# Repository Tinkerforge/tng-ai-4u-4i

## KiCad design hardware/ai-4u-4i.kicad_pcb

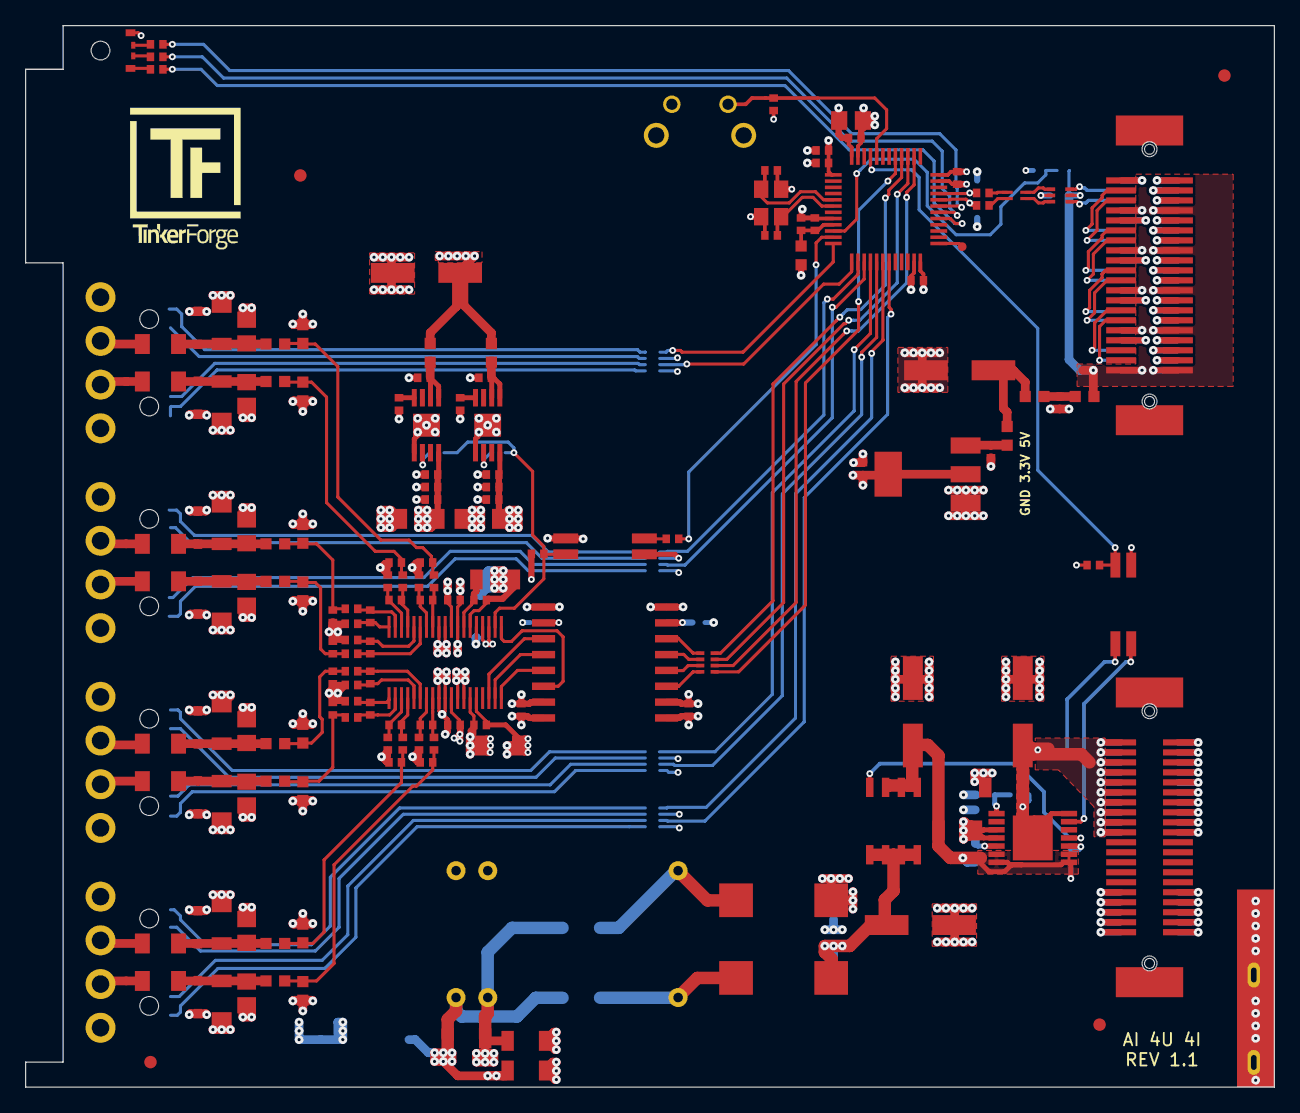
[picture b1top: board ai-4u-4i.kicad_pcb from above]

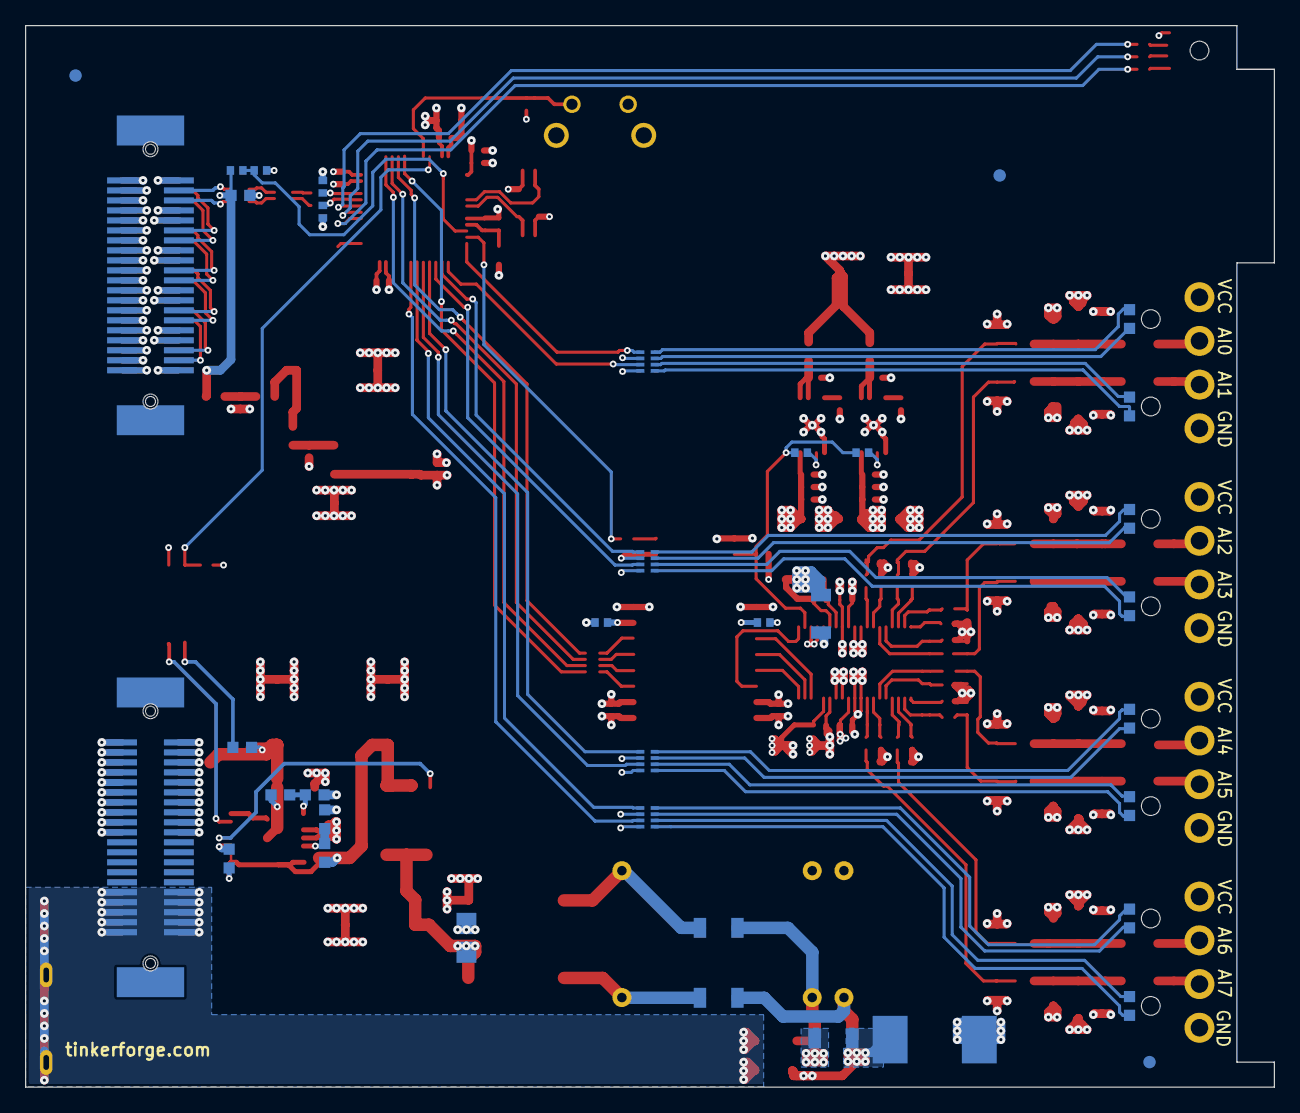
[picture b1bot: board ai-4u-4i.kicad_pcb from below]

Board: 4 copper layers, 100.0 x 85.0 mm, 206 parts (38 on the bottom side), 141 nets.

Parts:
C101, C102, C116, C117, C226, C227, C228, C229, C236, C237, C240, C241, C242, C243: 1uF; C0402F
C103, C104, C105, C106, C107, C112, C233, C235, C244, C245: 100nF; C0402F
C108, C109: 33pF; C0402F
C110: 10uF; C0805E
C111: 100uF; ELKO_63
C113, C114: 47pF; C0402F
C115: 2.2uF; C0603F
C118: 10uF/50V; C1206
C119, C120: 0; C1206
C121, C125, C126: 10uF/35V; C1206
C122, C123, C124, C234: 100uF/35V; ELKO_63
C127, C128: 1nF/2kV; C1206
C201, C202, C203, C204, C205, C206, C207, C208: 22nF; C1206
C209, C210, C211, C212, C213, C214, C215, C216: 2200pF; C0603F
C217, C218, C219, C220, C221, C222, C223, C224, C238, C239: 10nF; C0402F
C225, C232, C246: 22uF; C1206
C230, C231: 10uF; C1206
D101: 3.0SMI30CATR; SMC
D201, D202, D211, D212, D213, D214, D215, D216: CDSOD323-T12C; SOD-323
D203, D204, D205, D206, D207, D208, D209, D210: LED; LED-LP
Fiducial_Mark: VAL**; Fiducial_Mark
Fiducial_Mark#2, Fiducial_Mark#3, Fiducial_Mark#4, Fiducial_Mark#5, Fiducial_Mark#6, Fiducial_Mark#7: VAL**; Fiducial_Mark
J101: TNG-Power-TOP; TNG-40-TOP
J102: TNG-Power-BTM; TNG-40-BTM
J103: TNG-Data-TOP; TNG-40-TOP
J104: TNG-Data-BTM; TNG-40-BTM
L101: FB; R0603F
L102, L103, L104: INDUCTs; R0603F
L105: 744230900; WE-CNSW-0603
L201, L202: FB; C0603F
LED101: EASV3015RGBA0; LED-RGB-LP
P102: Debug; DEBUG_PAD
P103: PE; PE_Hook
P201: INPUT0; OQ_4P
P202: INPUT1; OQ_4P
P203: INPUT2; OQ_4P
P204: INPUT3; OQ_4P
Q101: FDS8449; SOIC-8-MOSFET
R101, R107, R108, R253: 1k; R0402F
R102, R105, R233, R235, R237, R239, R241, R243, R245, R247: 0; R0402F
R103, R104: 22; R0402F
R106: 56; R0402F
R109: 10k; R0402F
R110, R115: 10k; R0603F
R111, R112: DNP; R0603F
R113: 22; R0603F
R114: 68k; R0603F
R116: VC1206K201R030; R1206
R201, R202, R203, R204, R205, R206, R207, R208: 100; RMELF
R209, R211, R213, R215: DNP; R0805E
R210, R212, R214, R216: 124; R0805E
R217, R218, R219, R220, R221, R222, R223, R224: 1k; R0603F
R225, R226, R227, R228, R229, R230, R231, R232: 10M; R0402F
R234, R236, R238, R240, R242, R244, R246, R248: 1.1k; R0402F
R251, R252, R254: 4.7k; R0402F
R256, R257: DNP; R0402F
RP201, RP202, RP203, RP204, RP206: 470; 4X0402
SW101: BOOT; TACT-6MM-HOR
T101: 744273222; WE-SL5
U101: STM32F070CBT6; LQFP48
U102: AZ1117EH; SOT-223
U103: 82400152; SOT563-SPEC
U104: DNP; TEL10
U105, U202: TLP293; SOP4
U106: STEF01; HTSSOP14
U201: ADS8698; TSSOP38
U203: ISO7741DWR; SOIC16_WIDE
U204: TPS7A6650QDGNRQ1; MSOP-8-EP
U205: TPS7A6633QDGNRQ1; MSOP-8-EP
X101: 8MHz; CRYSTAL_3225

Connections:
3V3: C101.1, C103.1, C104.1, C105.1, C106.1, C110.1, C116.1, C235.1, L101.1, LED101.1, R109.2, R254.1, RP201.2, RP201.4, RP202.2, RP202.4, RP203.2, RP203.4, RP204.2, RP204.4, SW101.1, U101.1, U101.24, U101.36, U101.48, U102.2, U202.1, U203.1
5VA: C115.1, J103.7, J103.8, J103.15, J103.16, J103.23, J103.24, J103.31, J103.32, J103.39, J103.40, J104.7, J104.8, J104.15, J104.16, J104.23, J104.24, J104.31, J104.32, J104.39, J104.40, L104.1, R107.1, U103.5
+5V: C111.1, L102.1, L103.2
ADC-RESET: R253.1, U101.11
AGND: C118.2, C120.1, C128.2, C201.2, C202.2, C203.2, C204.2, C205.2, C206.2, C207.2, C208.2, C209.2, C210.2, C211.2, C212.2, C213.2, C214.2, C215.2, C216.2, C225.2, C226.2, C227.2, C228.1, C229.2, C230.2, C231.1, C232.1, C233.2, C234.2, C236.1, C237.1, C238.1, C239.1, C240.2, C241.2, C242.2, C243.2, C244.1, C245.1, C246.2, D101.2, D201.2, D202.2, D211.2, D212.2, D213.2, D214.2, D215.2, D216.2, P201.4, P202.4, P203.4, P204.4, R116.2, R209.1, R210.1, R211.1, R212.1, R213.1, R214.1, R215.1, R216.1, R225.1, R226.1, R227.1, R228.1, R229.1, R230.1, R231.1, R232.1, R234.2, R236.2, R238.2, R240.2, R242.2, R244.2, R246.2, R248.2, U104.10, U201.3, U201.4, U201.6, U201.8, U201.10, U201.11, U201.28, U201.29, U201.31, U201.32, U201.33, U202.3, U203.9, U203.15, U204.5, U204.EP, U205.5, U205.EP
AGNDA: C121.2, C122.2, C123.2, C124.2, C125.2, C126.2, J101.2, J101.4, J101.6, J101.8, J101.10, J101.12, J101.14, J101.16, J101.18, J101.20, J102.1, J102.3, J102.5, J102.7, J102.9, J102.11, J102.13, J102.15, J102.17, J102.19, R112.2, R115.2, T101.2, U106.3, U106.4
AIN0: R107.2, R108.1, U101.10
AIN0_N: C218.2, R236.1, U201.17
AIN0_P: C218.1, R235.1, U201.16
AIN1_N: C219.2, R238.1, U201.19
AIN1_P: C219.1, R237.1, U201.18
AIN2_N: C222.2, R244.1, U201.20
AIN2_P: C222.1, R243.1, U201.21
AIN3_N: C223.2, R246.1, U201.22
AIN3_P: C223.1, R245.1, U201.23
AIN4_N: C221.2, R242.1, U201.24
AIN4_P: C221.1, R241.1, U201.25
AIN5_N: C224.2, R248.1, U201.26
AIN5_P: C224.1, R247.1, U201.27
AIN6_N: C217.2, R234.1, U201.13
AIN6_P: C217.1, R233.1, U201.12
AIN7_N: C220.2, R240.1, U201.15
AIN7_P: C220.1, R239.1, U201.14
AVDD: C225.1, C227.1, C229.1, C240.1, C242.1, C244.2, U201.9, U201.30, U204.8
DVDD: C226.1, C230.1, C233.1, C241.1, C243.1, C245.2, C246.1, R251.2, R252.2, U201.34, U203.16, U205.8
Earth: C127.2, C128.1, J101.31, J101.32, J101.33, J101.34, J101.35, J101.36, J101.37, J101.38, J101.39, J101.40, J102.31, J102.32, J102.33, J102.34, J102.35, J102.36, J102.37, J102.38, J102.39, J102.40, P103.1
GND: C101.2, C102.2, C103.2, C104.2, C105.2, C106.2, C107.2, C108.1, C109.1, C110.2, C111.2, C112.2, C113.2, C114.2, C115.2, C116.2, C117.2, C235.2, J103.1, J103.2, J103.4, J103.6, J103.9, J103.10, J103.12, J103.14, J103.17, J103.18, J103.20, J103.22, J103.25, J103.26, J103.28, J103.30, J103.33, J103.34, J103.36, J103.38, J104.1, J104.2, J104.3, J104.5, J104.9, J104.10, J104.11, J104.13, J104.17, J104.18, J104.19, J104.21, J104.25, J104.26, J104.27, J104.29, J104.33, J104.34, J104.35, J104.37, R101.1, R108.2, U101.8, U101.23, U101.35, U101.47, U102.1, U103.2, U105.3, U203.2, U203.8, X101.3
LED0: RP201.1, U101.12
LED1: RP201.3, U101.13
LED2: RP202.1, U101.14
LED3: RP202.3, U101.15
LED4: RP203.1, U101.16
LED5: RP203.3, U101.17
LED6: RP204.1, U101.18
LED7: RP204.3, U101.19
LEDB: R106.1, U101.31
LEDG: R105.1, U101.30
LEDR: R102.1, U101.29
unnamed: C102.1, C107.1, L101.2, U101.9
unnamed: C108.2, U101.5, X101.2
unnamed: C109.2, U101.6, X101.1
unnamed: C112.1, L103.1, L104.2
unnamed: C117.1, L102.2, U102.3
unnamed: C119.2, T101.4, U104.16
unnamed: C120.2, T101.3, U104.1
unnamed: C121.1, C123.1, Q101.D, T101.1
unnamed: C201.1, D201.1, R201.2, R209.2, R217.2
unnamed: C202.1, D202.1, R202.2, R210.2, R218.2
unnamed: C203.1, D211.1, R203.2, R211.2, R219.2
unnamed: C204.1, D212.1, R204.2, R212.2, R220.2
unnamed: C205.1, D213.1, R205.2, R213.2, R221.2
unnamed: C206.1, D214.1, R206.2, R214.2, R222.2
unnamed: C207.1, D215.1, R207.2, R215.2, R223.2
unnamed: C208.1, D216.1, R208.2, R216.2, R224.2
unnamed: C209.1, R217.1, R225.2, R233.2
unnamed: C210.1, R218.1, R226.2, R235.2
unnamed: C211.1, R219.1, R227.2, R237.2
unnamed: C212.1, R220.1, R228.2, R239.2
unnamed: C213.1, R221.1, R229.2, R241.2
unnamed: C214.1, R222.1, R230.2, R243.2
unnamed: C215.1, R223.1, R231.2, R245.2
unnamed: C216.1, R224.1, R232.2, R247.2
unnamed: C228.2, C232.2, U201.7
unnamed: C231.2, U201.5
unnamed: C236.2, L201.1, U204.1, U204.2
unnamed: C237.2, L202.1, U205.1, U205.2
unnamed: C238.2, U204.4
unnamed: C239.2, U205.4
unnamed: D203.1, RP201.7
unnamed: D203.2, RP201.8
unnamed: D204.1, RP201.5
unnamed: D204.2, RP201.6
unnamed: D205.1, RP202.7
unnamed: D205.2, RP202.8
unnamed: D206.1, RP202.5
unnamed: D206.2, RP202.6
unnamed: D207.1, RP203.7
unnamed: D207.2, RP203.8
unnamed: D208.1, RP203.5
unnamed: D208.2, RP203.6
unnamed: D209.1, RP204.7
unnamed: D209.2, RP204.8
unnamed: D210.1, RP204.5
unnamed: D210.2, RP204.6
unnamed: J103.3, J104.12
unnamed: J103.5, J104.14
unnamed: J103.11, J104.20
unnamed: J103.13, J104.22
unnamed: J103.19, J104.28
unnamed: J103.21, J104.30
unnamed: J103.27, J104.36
unnamed: J103.29, J104.38
unnamed: LED101.2, R106.2
unnamed: LED101.3, R105.2
unnamed: LED101.4, R102.2
unnamed: P102.1, U101.25
unnamed: P201.2, R201.1
unnamed: P201.3, R202.1
unnamed: P202.2, R203.1
unnamed: P202.3, R204.1
unnamed: P203.2, R205.1
unnamed: P203.3, R206.1
unnamed: P204.2, R207.1
unnamed: P204.3, R208.1
unnamed: Q101.G, U106.11
unnamed: R101.2, SW101.2, U101.44
unnamed: R110.2, U105.1
unnamed: R111.2, R112.1, U106.5
unnamed: R113.2, U106.10
unnamed: R114.2, R115.1, U106.1
unnamed: R252.1, U203.10
unnamed: R253.2, U202.2
unnamed: R254.2, U203.7
unnamed: R256.2, U204.6
unnamed: R257.2, U205.6
unnamed: RP206.5, U203.6
unnamed: RP206.6, U203.5
unnamed: RP206.7, U203.4
unnamed: RP206.8, U203.3
unnamed: U201.1, U203.14
unnamed: U201.36, U203.11
unnamed: U201.37, U203.12
unnamed: U201.38, U203.13
PWR_GOOD: R109.1, U101.45, U105.4
PWR_PG: U105.2, U106.13
SPI-CLK: RP206.3, U101.39
SPI-CS: RP206.2, U101.38
SPI-MISO: RP206.4, U101.40
SPI-MOSI: RP206.1, U101.41
USB-DM: C114.1, R104.2, U101.32
USB-DMA: J104.6, U103.4
USB-DMB: L105.1, U103.3
USB-DMC: L105.2, R104.1
USB-DP: C113.1, R103.2, U101.33
USB-DPA: J104.4, U103.6
USB-DPB: L105.4, U103.1
USB-DPC: L105.3, R103.1
VCC: C118.1, C119.1, C127.1, C234.1, D101.1, L201.2, L202.2, P201.1, P202.1, P203.1, P204.1, R116.1, U104.9
VCCPWRA: C122.1, C126.1, J101.1, J101.3, J101.5, J101.7, J101.9, J101.11, J101.13, J101.15, J101.17, J101.19, J102.2, J102.4, J102.6, J102.8, J102.10, J102.12, J102.14, J102.16, J102.18, J102.20, R110.1, R114.1, U106.14, U106.EXP
VO: C124.1, C125.1, Q101.S, R111.1, R113.1, U106.6, U106.7, U106.8, U106.9
_RESET: R251.1, R256.1, R257.1, U201.2, U202.4

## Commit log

2019-12-10 add readme
2019-12-20 analog input schematic started
2019-12-23 increase rgb led diameter
2019-12-23 more schematic
2019-12-30 schematic finished
2019-12-30 fix inductor footprint
2019-12-30 placement finished, some routing
2020-01-02 fully routed
2020-01-02 small improvement
2020-01-02 add stuff
2020-01-02 improve vcc routing
2020-03-02 add hook footprint
2020-05-14 fix values
2020-05-14 specify value
2020-06-09 part specification
2020-06-23 Add datasheets
2020-06-23 Add .gitignore
2020-06-23 Add initial stub firmware
2020-06-26 add hint
2020-07-20 Add driver for ADS8698 and initial simplified API
2020-07-27 Use HAL config from bricklib2
2020-07-27 Add TIM defines for status LEDs
2020-09-04 add version 1.1 * fix footprints, improve routing
2020-09-04 improve routing
2020-09-04 fix text layer
2020-09-04 fix footprint
2020-09-08 fix footprints
2020-09-08 all footprints updated
2020-09-10 fix 3d stuff

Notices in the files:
hardware/ai-4u-4i.kicad_pcb:
Licensed under CERN OHL v.1.1
Copyright (©) 2020, B.Nordmeyer
Copyright Tinkerforge GmbH 2020.
This documentation describes Open Hardware and is licensed under the
CERN OHL v. 1.1.
